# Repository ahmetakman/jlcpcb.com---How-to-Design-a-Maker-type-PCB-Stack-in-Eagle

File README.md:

# jlcpcb.com---How-to-Design-a-Maker-type-PCB-Stack-in-Eagle

In this text, we would provide necessary instructions for designing PCB stacks in a simple sense. After designing your PCB stack, you can easily materialize your designs using JLCPCB's super-simple interface. Thanks to JLCPCB, our precious readers and dear makers can acquire high quality PCBs and pay less than others.

Makers generally do not prefer designing PCBs by a modular approach. But in iterative design processes, in which designers gradually change their designs during the prototyping phase, it could lower the price and benefit the maker by avoiding the manufacturing of the whole PCB multiple times.

Now, Let's dive in and explain how you can design your own PCB stack.

Supplies:
https://jlcpcb.com

Step 1: Drawing a Schematic
Drawing a Schematic
Initial step for designing a PCB is making a schematic of the electrical components and their connections. Designing a modular PCB stack is no different. Firstly, you should open a new schematic file in your PCB designing software. Autodesk Eagle is the preffered software for this text. After you've done that, you should add your components. Most softwares only allow you to add them one by one. Then, you should connect your components with wiring tool. Then, you should name your connections for readability. This would allow our software to create connections automaticly when we turn this schematic into a PCB.

2: Completing Your Board Design
Completing Your Board Design
After completing your schematic design, click "Switch to Board" button on Eagle interface. This would automatically transform your schematic design into a PCB design. During this phase, you can reorganize the wirings and make your PCB simpler and easier to produce. But thanks to JLCPCB, there is no need to do that because there is no PCB they cannot produce. After this phase, Our PCB's skeleton is ready.

Step 3: Exporting Your PCB Design As DXF

DXF format is used for creating a template of our PCB. This allows us to create multiple layers of PCBs with same fundamental holes; Therefore, we will be able to create a pcb stack with those layers.

Step 4: Importing DXF and Designing PCB Layers

After exporting your fundamental design as DXF, we should import it in order to use it as a template . Then, we will create our layers from schematic step using that template, so we would easily recognize the mutual connections and create a completely compatible PCB stack. Now, our pcb stack is as good as ready.

Step 5: Why Should You Choose to Design Modular PCBs
Modular designs are always a life saver if you encounter an error during your project. You could immediately find which board is causing that error and your whole design does not get affected by that error. A simple change in the design of that particular board would be enough to save your project and it would be significantly cheaper than changing the whole design. If you are working on a project that has multiple objectives, that flexibility on your design not only would let you focus on the problems part by part, but also make the problems simpler by dividing them into multiple parts.

Step 6: Manufacturing Your PCBs
After doing a great job on design, We believe that your PCB design deserves the best. You can send your beautiful PCB designs to JLCPCB for the best feasable manufacturing option available on our planet.
You can reach this article from this link : https://www.instructables.com/How-to-Design-a-Maker-type-PCB-Stack-in-Eagle/

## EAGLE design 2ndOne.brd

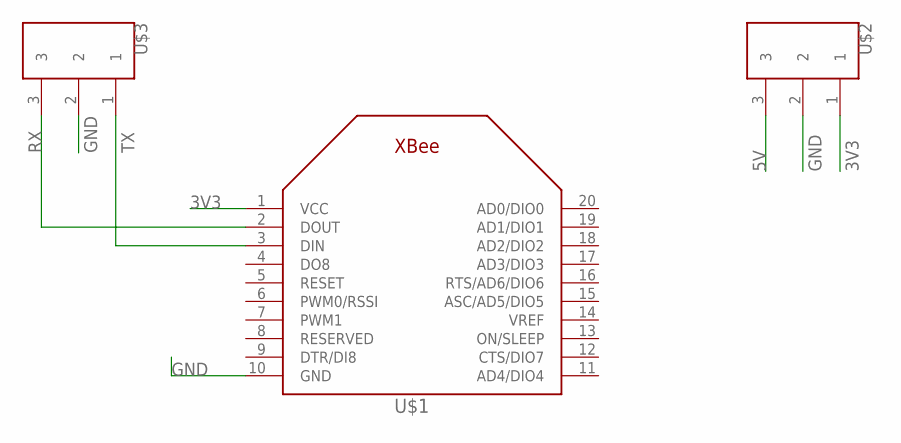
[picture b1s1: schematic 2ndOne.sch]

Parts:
U$1: XBEE
U$2, U$3: PIN3; 3PIN

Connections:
3V3: U$1.1 (VCC), U$2.1
5V: U$2.3
GND: U$1.10 (GND), U$2.2, U$3.2
RX: U$1.2 (DOUT), U$3.3
TX: U$1.3 (DIN), U$3.1

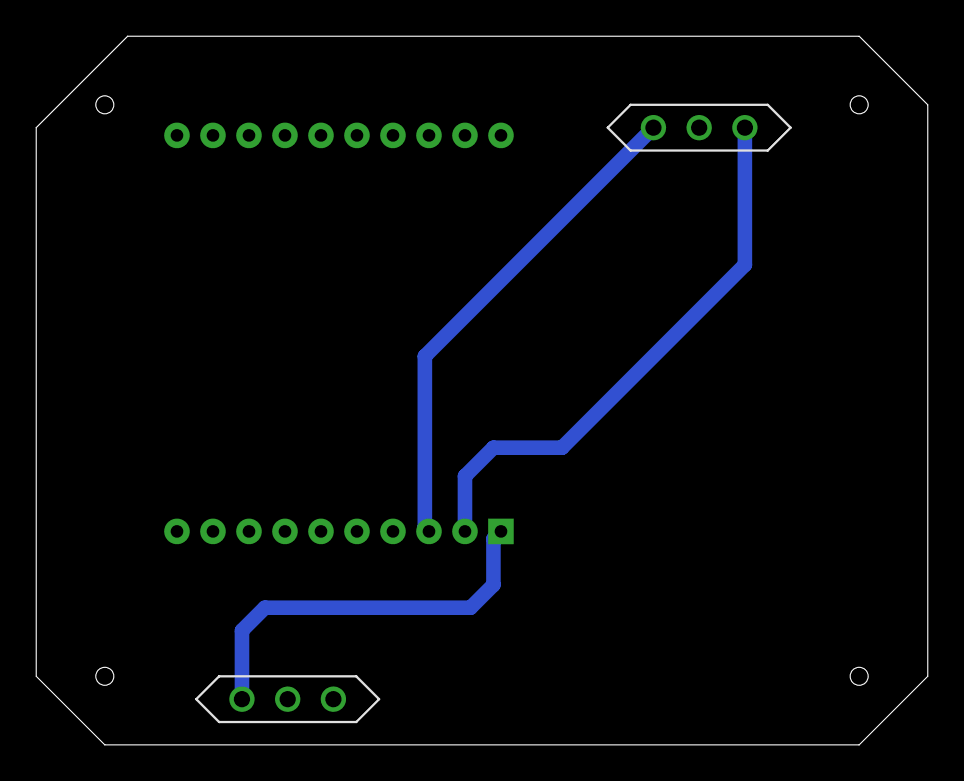
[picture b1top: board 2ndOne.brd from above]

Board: 2 copper layers, 49.5 x 39.4 mm, 3 parts (1 on the bottom side), 4 nets.

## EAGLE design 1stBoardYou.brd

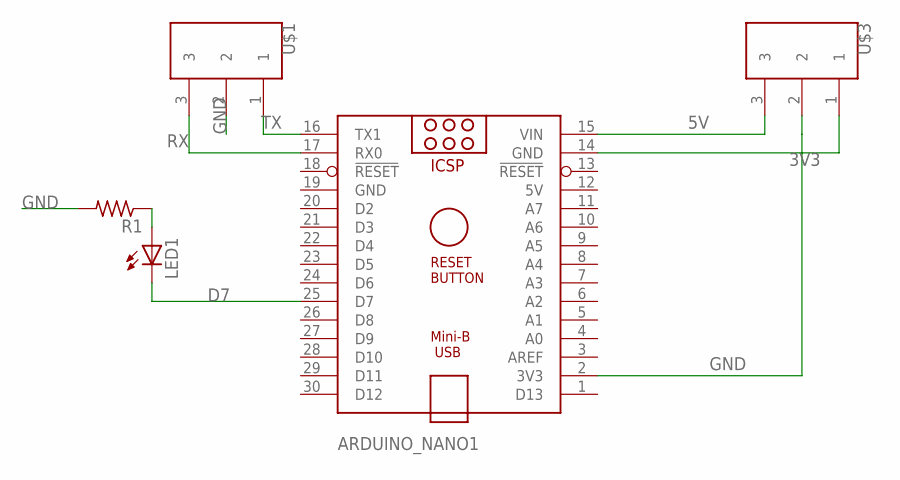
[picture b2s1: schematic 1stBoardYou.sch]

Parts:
ARDUINO_NANO1: ARDUINO_NANO
LED1: LED3MM
R1: FLIPFLOP-RES; 0805-THM
U$1, U$3: PIN3; 3PIN

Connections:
3V3: ARDUINO_NANO1.2 (3V3), U$3.2
5V: ARDUINO_NANO1.12 (5V), ARDUINO_NANO1.15 (VIN), U$3.3
D7: ARDUINO_NANO1.25 (D7), LED1.K (C)
GND: ARDUINO_NANO1.14 (GND), ARDUINO_NANO1.19 (GND), R1.2, U$1.2, U$3.1
unnamed: LED1.A, R1.1
RX: ARDUINO_NANO1.17 (RX0), U$1.3
TX: ARDUINO_NANO1.16 (TX1), U$1.1

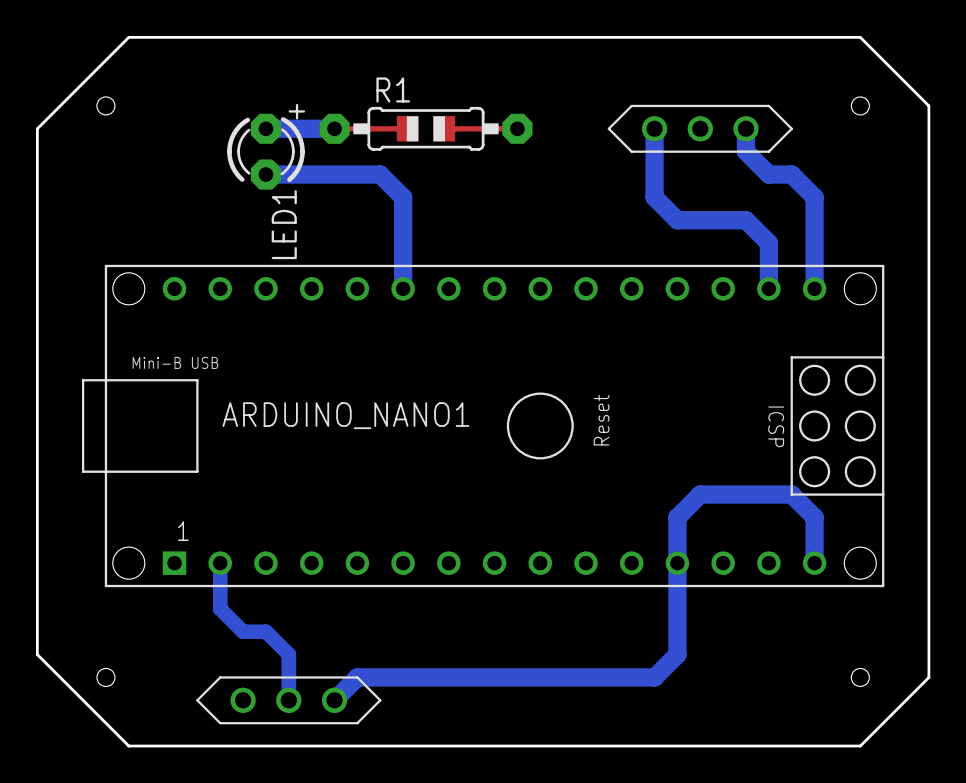
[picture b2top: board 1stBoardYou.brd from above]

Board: 2 copper layers, 49.5 x 39.4 mm, 5 parts (0 on the bottom side), 7 nets.
